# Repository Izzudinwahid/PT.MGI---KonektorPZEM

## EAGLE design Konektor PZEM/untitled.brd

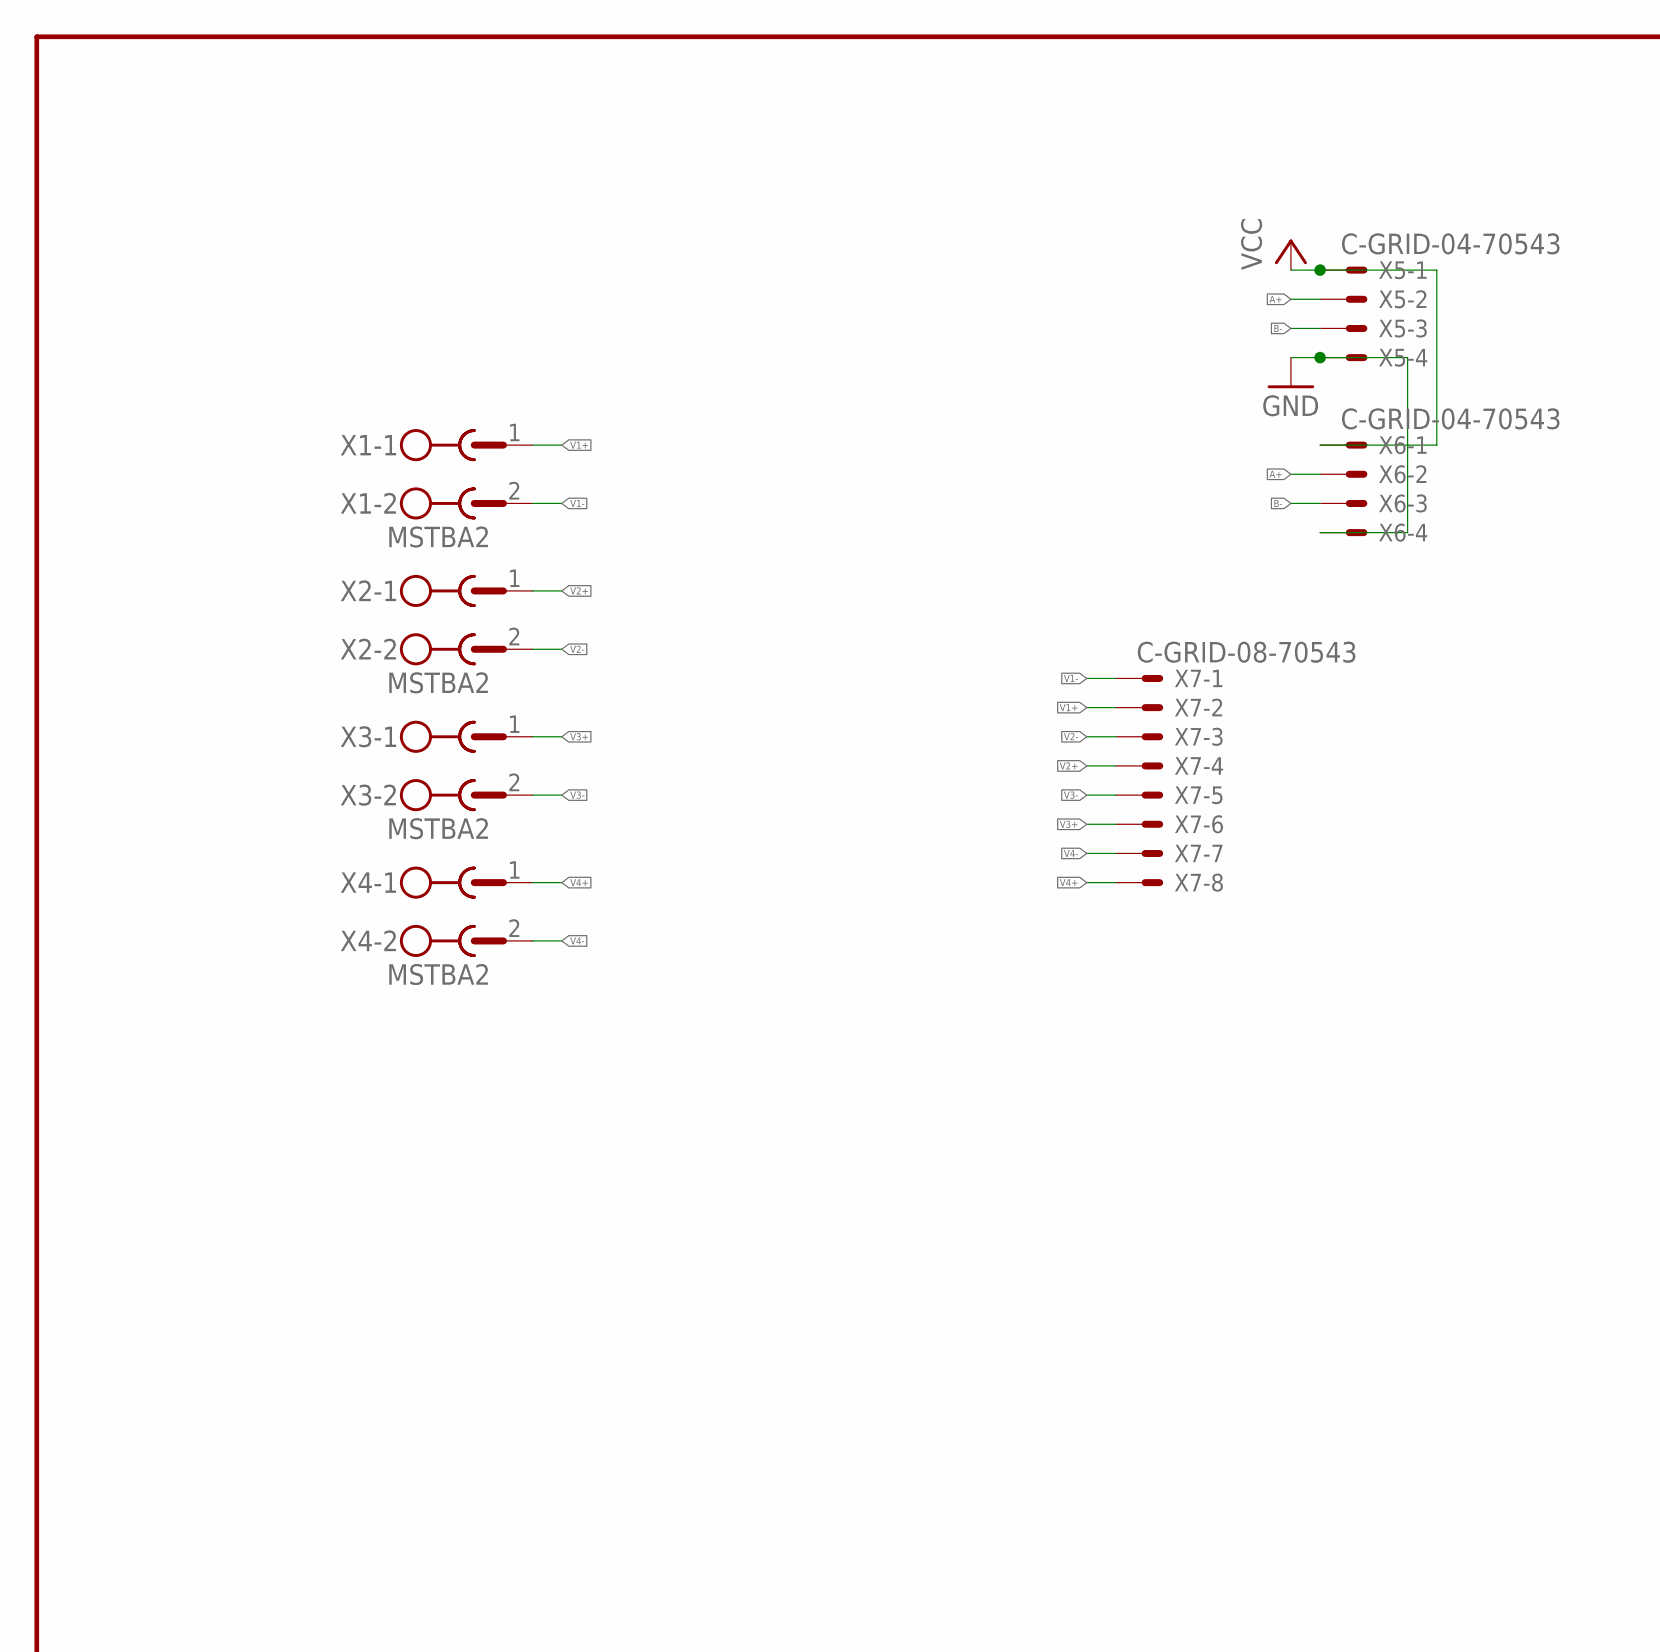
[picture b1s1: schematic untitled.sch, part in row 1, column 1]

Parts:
X1, X2, X3, X4: MSTBA2
X5, X6: C-GRID-04-70543; 70543-04
X7: C-GRID-08-70543; 70543-08

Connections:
A+: X5.2, X6.2
B-: X5.3, X6.3
GND: X5.4, X6.4
V1+: X1.1, X7.2
V1-: X1.2, X7.1
V2+: X2.1, X7.4
V2-: X2.2, X7.3
V3+: X3.1, X7.6
V3-: X3.2, X7.5
V4+: X4.1, X7.8
V4-: X4.2, X7.7
VCC: X5.1, X6.1

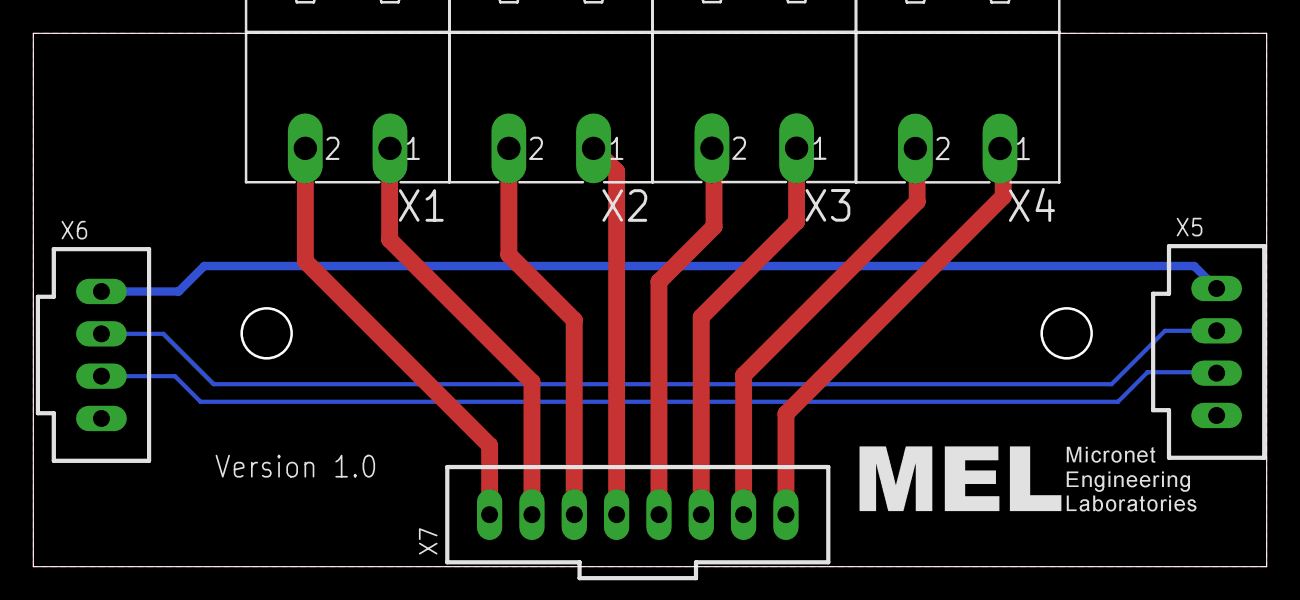
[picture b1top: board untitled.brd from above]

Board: 2 copper layers, 74.0 x 32.0 mm, 7 parts (0 on the bottom side), 12 nets.

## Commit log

2024-08-16 PCB v1.0
